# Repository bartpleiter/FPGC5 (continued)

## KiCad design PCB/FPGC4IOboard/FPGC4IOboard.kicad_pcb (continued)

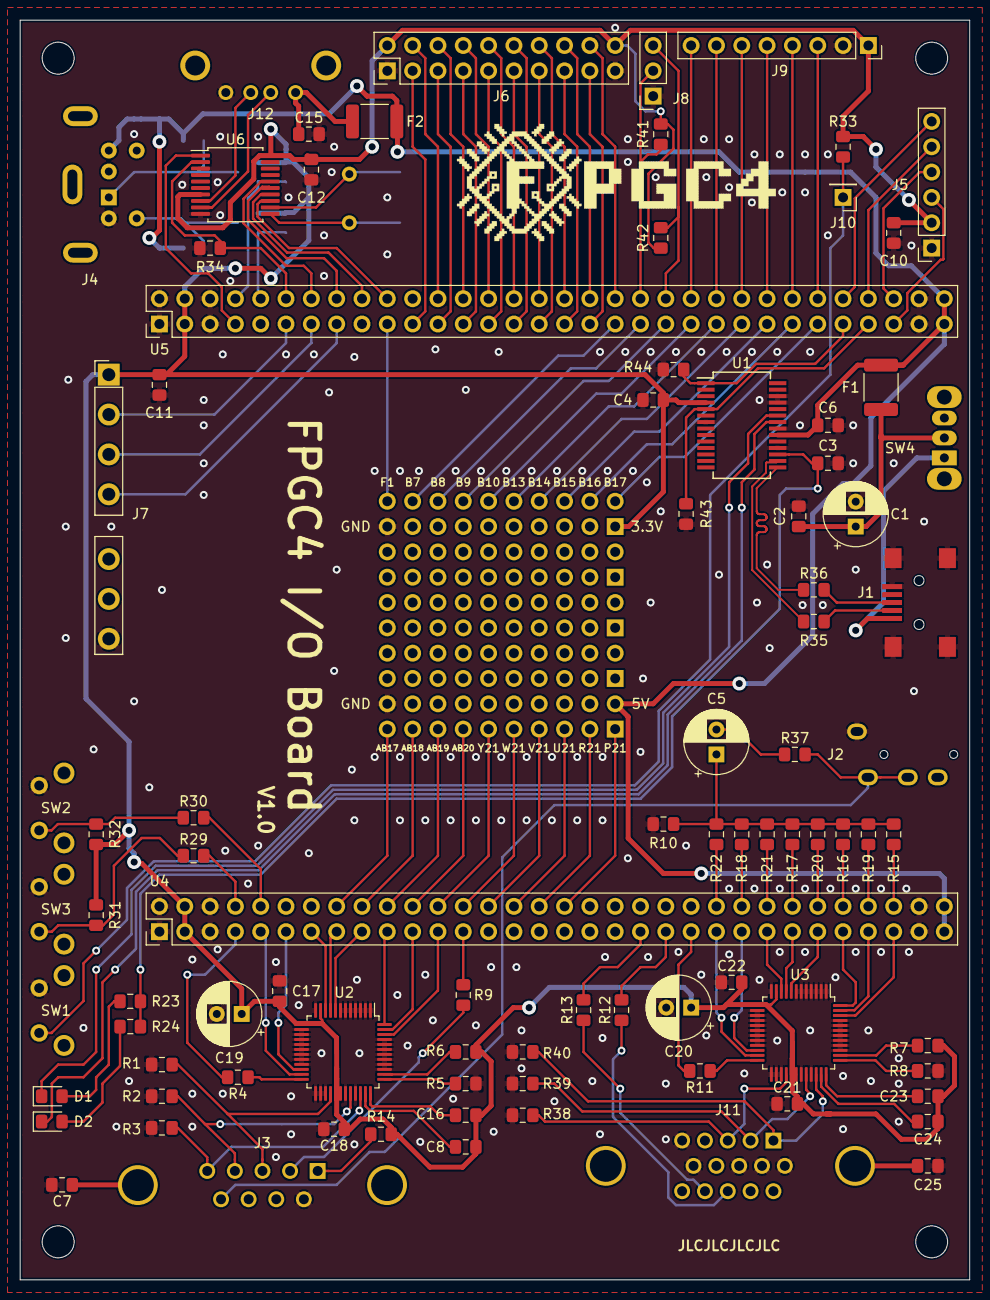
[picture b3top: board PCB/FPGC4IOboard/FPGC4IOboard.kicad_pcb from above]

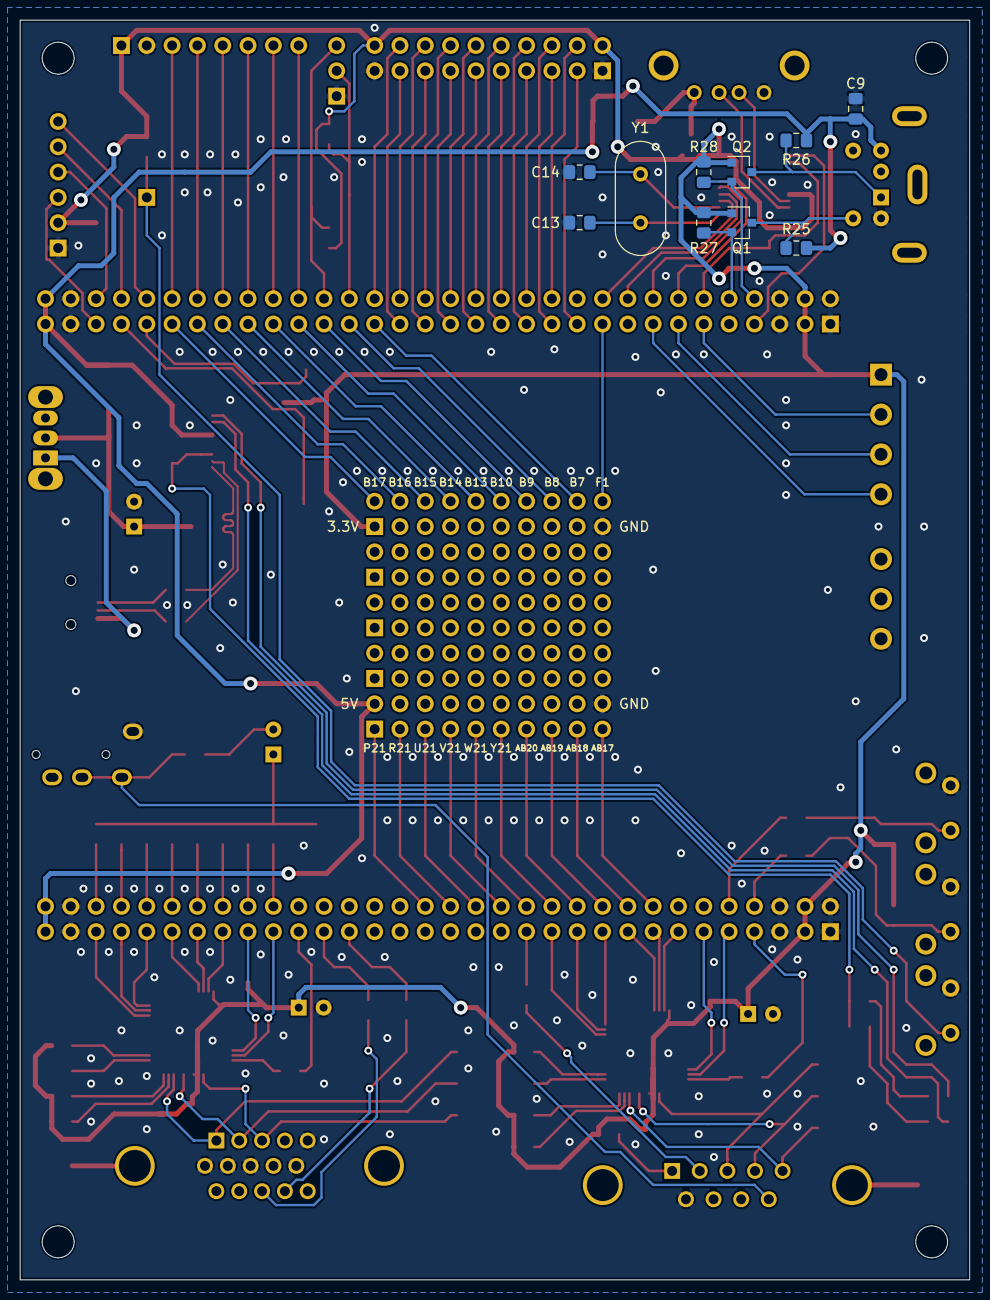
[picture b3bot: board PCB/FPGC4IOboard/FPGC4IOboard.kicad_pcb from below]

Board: 2 copper layers, 95.2 x 126.4 mm, 101 parts (10 on the bottom side), 141 nets.

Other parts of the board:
LOGO: LOGO

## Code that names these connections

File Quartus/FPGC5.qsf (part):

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set_location_assignment PIN_E1 -to SPI2_miso
set_location_assignment PIN_H1 -to SPI2_rst
set_location_assignment PIN_F1 -to SPI2_nint
set_location_assignment PIN_A3 -to PS2_data
set_location_assignment PIN_B2 -to PS2_clk
set_location_assignment PIN_A19 -to SPI3_cs
set_location_assignment PIN_B20 -to SPI3_clk
set_location_assignment PIN_A20 -to SPI3_mosi
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set_location_assignment PIN_D21 -to TMDS_n[1]
set_location_assignment PIN_C22 -to TMDS_p[0]
set_location_assignment PIN_C21 -to TMDS_n[0]
set_location_assignment PIN_C1 -to led_Booted
set_location_assignment PIN_AB17 -to led_Eth
set_location_assignment PIN_AB19 -to led_Flash
set_location_assignment PIN_B1 -to led_USB0
set_location_assignment PIN_AB20 -to led_USB1
set_location_assignment PIN_AB13 -to led_PS2
set_location_assignment PIN_AB16 -to led_HDMI
set_location_assignment PIN_AB18 -to led_QSPI
set_location_assignment PIN_AB15 -to led_GPU
set_location_assignment PIN_AB14 -to led_I2S
set_location_assignment PIN_B6 -to I2S_SDIN
set_location_assignment PIN_B5 -to I2S_SCLK
set_location_assignment PIN_C4 -to I2S_LRCLK
set_location_assignment PIN_B4 -to I2S_MCLK
set_location_assignment PIN_Y21 -to composite[0]
set_location_assignment PIN_W21 -to composite[1]
set_location_assignment PIN_V21 -to composite[2]
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
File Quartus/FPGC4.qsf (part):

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set_location_assignment PIN_W1 -to SDRAM_A[10]
set_location_assignment PIN_Y4 -to SDRAM_A[11]
set_location_assignment PIN_V6 -to SDRAM_A[12]
set_location_assignment PIN_AA20 -to crt_clk
set_location_assignment PIN_AA19 -to crt_sync
set_location_assignment PIN_P22 -to crt_r[2]
set_location_assignment PIN_N22 -to crt_r[1]
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set_location_assignment PIN_R22 -to crt_g[0]
set_location_assignment PIN_Y22 -to crt_b[1]
set_location_assignment PIN_W22 -to crt_b[0]
set_location_assignment PIN_J22 -to vga_clk
set_location_assignment PIN_L22 -to vga_hs
set_location_assignment PIN_K22 -to vga_vs
set_location_assignment PIN_B19 -to UART0_dtr
set_location_assignment PIN_B20 -to UART0_out
set_location_assignment PIN_B18 -to UART0_in
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set_location_assignment PIN_C2 -to SPI2_miso
set_location_assignment PIN_B1 -to SPI2_rst
set_location_assignment PIN_B2 -to SPI2_nint
set_location_assignment PIN_P1 -to PS2_data
set_location_assignment PIN_R1 -to PS2_clk
set_location_assignment PIN_N1 -to SNES_clk
set_location_assignment PIN_M1 -to SNES_latch
set_location_assignment PIN_J1 -to SNES_data
set_location_assignment PIN_A18 -to SPI3_cs
set_location_assignment PIN_A19 -to SPI3_clk
set_location_assignment PIN_A20 -to SPI3_mosi
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
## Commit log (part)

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2021-06-23 Init from FPGC4
2021-06-23 Migration from FSX3 devlopment to Quartus folder
2021-06-23 Migrated FSX3 development to Verilog folder
2021-06-23 Updated Quartus project to new FPGC5 name
2021-06-23 Added last Quartus file
2021-06-23 Recompiled Quartus project to verify new version
2021-06-24 Added light sleep on idle to save power
2021-06-24 Fixed midiSynth. Few quick fixes to run some uart related scripts on WSL2 via Windows.
2021-06-25 Updated and tested all scripts to work in WSL2
2021-06-25 userBDOS MIDI program now works (as a test, should make proper audio library. Changed BDOS Alpha to BDOS. Changed command names to ls and cd. Added a warning in BDOS documentation about the used of t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
2021-06-26 Started simulation of CPU
2021-06-27 CPU now only uses posegde clocks. Improved some CPU simulation stuff. Memory Unit remains to be improved
2021-06-28 Added simulation of entire FPGC, useful for testing new MU timings
2021-06-30 New MU bus design. SDRAM controller to 100MHz, all works in simulation but not in hardware. All works when SDRAM back at 25MHz and negedge clock, so the problem is not the new bus and MU design. Need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
2021-07-01 FPGC5 now works with SDRAM at 100MHz, tested in hardware. Still quite messy and MU contains extra cycles to latch certain things to prevent combinational loops and to pass timing constraints.
2021-07-01 removed now ignored hidden quartus folder
2021-07-01 Added seperate 90 degrees phase shifted SDRAM (not controller) clock, and changed the controller back to posedge to satisfy timing contrainsts even better
2021-07-01 Fixed reset issue where the SDRAM controller regs were not reset in mu. Improved SDRAM controller and SPIreader timings. removed mu_q assignment in instruction decoder (now only latches it) since it 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
2021-07-04 Improved some IO modules
2021-07-05 New and better nespadreader, fixed bug in MU where bus_done_next would be instantly set when the address was higher than a certain address. Updated output_file. SPI modules are the only ones that sti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
2021-07-05 New SPI reader module. Replaces FastSPI module as well, even though it runs at max half system speed. Still need to do spi reader (qspi flash reader) module
2021-07-06 Updated system clock to 50MHz (from 25MHz) including modules that depended on a 25MHz clock. Cleaned up the Quartus project a bunch by removing unused files and pins (e.g. removed all vga/crt stuff a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
2021-07-06 Improved MU, much cleaner now. Did not improve on timing and area by much, probably because of the large address selection chain. However, it is now much easier to work in without having to worry too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
2021-07-08 Added compileAndSend script in Assembler. Renamed the simTest file
2021-07-09 Added userBDOS webserver program. Updated BDOS to use the same function for loading a program from storage. Netflasher and uploader now retries up to 5 times on failure with a second delay in between
2021-07-09 Modified netUpload to more easily allow for uploading any file. Added some execute permissions as well
2021-07-09 Updated documentation a bit. Added notes about not updating docs much
2021-07-12 UART speed from 115200 to 1MBaud (in HW, Tools and ESP32Synth). Added help command to BDOS. Started on cp command.
2021-07-12 Updated bootloader to not display the 4 in FPGC4. Also fixed graphics bug where the pattern table is not completely copied
2021-07-13 Changed scripts to linux. Set retries for BDOS upload/send to 10.
2021-07-13 updated gitignore
2021-07-13 removed .depend
2021-07-13 Implemented argument parsing and file reading
2021-07-14 Minor additions to new C compiler. Added directory listing to webServer
2021-07-14 Added (empty) files for new C compiler. Added test to makefile
2021-07-15 Added key holding for USB keyboard. Added backslash keys for keycode 50 and 100 (USB). Added uprintDec/Hex(ln) functions
2021-07-17 Fix in webserver where rbuf is now removed from the stack
2021-10-19 Started working on new FPGC5 PCB, starting to move back to linux (already changed some .gtkw paths), added script for creating a RGB332 to NTSC Y Phase Saturation lookup table
2021-10-20 Added 240p color NTSC video output! Can be selected by DIP[1] (selects between HDMI and NTSC). Currently gives timing errors, but works fine in hardware (afaik), need to find a way to tell quartus th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
2021-10-21 Added a bit to the C++ c compiler
2021-10-22 Fixed vertical position of NTSC output. Restored GPIO pin assignments and moved NTSC to the extra pins on the bottom of the PCB. Worked a tiny bit on the new PCB version. Added a cython base version 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
2021-10-22 Added some more cython conversion. Running into problem of multiple possible data type. Probably need to rewrite a lot later on to fix it
2021-10-24 Initial version of PCBv3 schema is done
2021-10-24 Ran annotation and fixed led footprints on schema
2021-10-27 Started on PCB layouting
2021-11-03 PCB v3 initial routing done. Need to optimize and finish silkscreen layer
2021-11-05 Basically finished the new PCB design
2021-11-21 Updated Quartus & Verilog to new PCB (v3) design. Added test code to test both CH376 chips. Added BOM of PCB in HTML. Fixed argument position bug in compileAndSend.sh
2021-11-26 Quick documentation update (new url without version number, readme change)
2021-11-27 Added LED visualizers. Fixed some small things like default CS and TX values (also on reset).
2021-11-28 Added SmallerC C compiler to the project, as attempt to create a better C compiler (that might eventually run on the FPGC itself). Still needs to be converted from either MIPS or X86 to B322. Removed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
2021-11-28 SmallerC small formatting updates. Added simple.c to use for converting basic stuff from MIPS to B322
2021-11-28 More progress on SimpleC B322 backend. Single call return now works and some basic stuff is converted now, like asm wrappers and some basic instructions
2021-11-30 Assembler now supports .code and .data directives (it moves all .data parts to the end of the program). Assembler now also supports .dl instructions (static label address as data). Assembler now also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
2021-11-30 removed labels from comments in assembler, since it does not work for instructions needing a second pass. Made difference between .rdata and .data, needed for an array of cstrings (pointers). More in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
2021-11-30 SmallerC backup commit, before trying to change all byte-addressable functionality to word-addressable. If this fails, I could temporarily duplicate .data statements
2021-11-30 Added .bss support to assembler. Modified compilerTests/m.c to generate a .bss section
2021-11-30 Bitwise operations now work in SmallerC
2021-11-30 Interrupts are now working
2021-12-01 Basic set of compiler tests now works for SmallerC
2021-12-01 Changed last few SimpleC instructions to B322. Only division and modulo remain, but I will probably just remove those and use a macro/function for that just like with ShivyC. Also changed multiline s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
2021-12-01 SmallerC now opens includes from the dicrecory of the source .c file
2021-12-01 Updated TODOs in SmallerC
2021-12-01 Added signed branch instructions to hardware and assembler (untested, but not a big change)
2021-12-01 Made all branch checks signed by default in SmallerC. Added a signed loop testcase. Replaced a lot of tabs with spaces.
2021-12-02 Fixed some constant bugs in SmallerC. Replaced division and modulo with a function so no more div or mod instructions are generated when compiling SmallerC using itself. Started on replacing some inc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
2021-12-02 Added os and bdos compiler flags to SmallerC, copied compile scripts
2021-12-02 Can now compile userBDOS programs with smallerC (tested by hotfixing Ccompiler/userBDOS stuff). Added makefile for bcc (eventual name of smallerC). Added .code segments for new wrappers
2021-12-03 removed instructions from bcc where parts of registers are cut off to 8 or 16 bits. Added file size print in compile script. gfx.c library done for now
2021-12-03 Fixed outdated comment in ASCII_BW.c
2021-12-03 updated gitignore with new BCC path
2021-12-04 Ported all HID functions to BCC. Improved USB keyboard button hold detection
2021-12-04 Ported FS and shell to BCC. Everything works including system calls/interrupt stuff. Only netloader remains before moving on to the userBDOS programs
2021-12-04 Ported netloader to BCC, adjusted some delay timings for the SPI stuff. BDOS is now fully working (and is faster and smaller)
2021-12-05 Ported wget over to BCC
2021-12-06 Started on some preprocessing things for running bcc on fpgc
2021-12-06 Removed more if(n)defs in userBDOS/bcc which will never be set for FPGC5 (in the near future of course, who knows if I will ever add a FP unit :P)
2021-12-07 More work on bcc on fpgc
2021-12-07 Started working on stdio replacement code (might eventually become a real library)
2021-12-07 fputs/c fgets are done now
2021-12-08 More stuffs. commented out some macros because of limited macro list
2021-12-08 ALU MULT is now always signed. More work on BCC on FPGC
2021-12-09 BCC on FPGC now seems to work decently, against all expectations. Need to make sure that getBDOSpath syscall always returns a terminated string
2021-12-11 Added file can open check in bcc on fpgc
2021-12-11 made annotations optional in BCC on FPGC. BCC on FPGC can now compile the webserver.c (although very slow). Added print in getc, since it is a nice progress bar alternative.
2021-12-12 Removed old files from project
2021-12-13 Started on assembler in C. Added newline prints for long .space commands in bcc on fpgc
2021-12-13 More progress on ASM
2021-12-14 Some documentation updates
2021-12-16 New flash programmer using BCC. Removed ShivyC. Added path backup when CD in BDOS
2021-12-16 Added progress bars in BDOS. Reduced error rate in netloader
2021-12-18 Changed RUN into ./ with proper argument support (BDOS). Added verify flash by default because it is really fast anyways. Moved bcc notes to documentation
2021-12-18 Created snake userBDOS game. Added syscall for obtaining the parsed usb keyboard buffer, useful for knowing if a certain button is held
2021-12-18 Fixed speed and game over bug in snake
2021-12-18 Removed left over debug print in userbdos/lib/sys.c
2021-12-18 Replaced memory addresses for paths and commands to global arrays. Fixed bug where shell would hang if a unknown command is 16 or more chars long. Created arrays and defines for cmd history in shell
2021-12-18 Fully implemented command history in shell. Does not write history to a file, because I am not sure if I want that yet
2021-12-19 Added done command in SPI flasher
2021-12-19 Added network HID support on port 3222. Keys can be sent using netcat, and depending on the machine stty -icanon should be used to directly send the keys when pressed. Also added wasd support in snak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
2021-12-20 Cleaned up BDOS.c code
2021-12-22 Implemented pass 1 in ASM
2021-12-22 Fixed linenumbers for labels in ASM
2021-12-23 ASM works now. Restructured some file and modified some files and filenames so they can be copied directly
2021-12-24 Added progress percentage for netloader
2022-01-11 Started on text editor
2022-01-11 More progress on text editor
2022-01-12 Added retries to netUpload/Flash.py. Created script that sends all userBDOS files to FPGC. Made seperate script to send single commands to BDOS. Had to add an echo in HIDloader for commands to know w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
2022-01-12 Made userBDOS programs use two spaces as tabs instead of four, for readability on FPGC
2022-01-13 Improved editor, now support pageup,down,end,home. Many fixes and improvements
2022-01-13 Reduced ASM size even further by moving a buffer from stdio
2022-01-13 Reduced size of BCC
2022-01-14 Minor fixes to text editor
2022-02-04 Removed CP placeholder from BDOS, as it will become a userBDOS program instead
2022-02-04 Created CP and MV programs
2022-02-04 Improved webserver mostly progress logging related, and fixed wrong comment in CP and MV code
2022-02-10 Added ASM optimizer option in the Python version which recursively removes all uncalled functions and global variables. Updated compile scripts to use this option and made some fixes to BDOS to preve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
2022-02-11 Added motion configuration file for HDMI capture streaming
